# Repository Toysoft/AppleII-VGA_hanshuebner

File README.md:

# ∀2 Retro Computing Analog VGA Card & PicoPal

This is a fork of
[David Kuder's version](https://github.com/V2RetroComputing/analog) of
[Mark Aikens' Apple II VGA](https://github.com/markadev/AppleII-VGA/)
project.

The goal of this fork is to make the board cheaper and easier to
produce.  It is now a 2 layer instead of a 4 layer PCB, uses cheaper
bus transceivers and 0603 passive components that are easier to work
with when building the board by hand.

The board provides a VGA output to Apple II compatible machines.  It works by
snooping the bus activity and capturing what is written to the internal
graphics hardware.  This is used to render an additional image into a
framebuffer on the Raspberry Pi Pico.  That framebuffer is output
to a standard VGA compatible output.

The VGA emulation starts up with a test screen.  Reset your Apple to
go to the BASIC prompt or boot screen.

The footprint of the VGA IDC connector on the board is incorrect.  The
red wire of the ribbon cable must be facing down, in direction of the 
motherboard.  If you get no picture, try rotating the cable.

Alternatively, the card can run a Z80 emulation in software, emulating
a standard Z80 softcard.  To use that mode, the Raspberry Pi Pico must
be re-flashed.

Please use
[GitHub Issues](https://github.com/hanshuebner/AppleII-VGA/issues) to
provide feedback.  THANK YOU!

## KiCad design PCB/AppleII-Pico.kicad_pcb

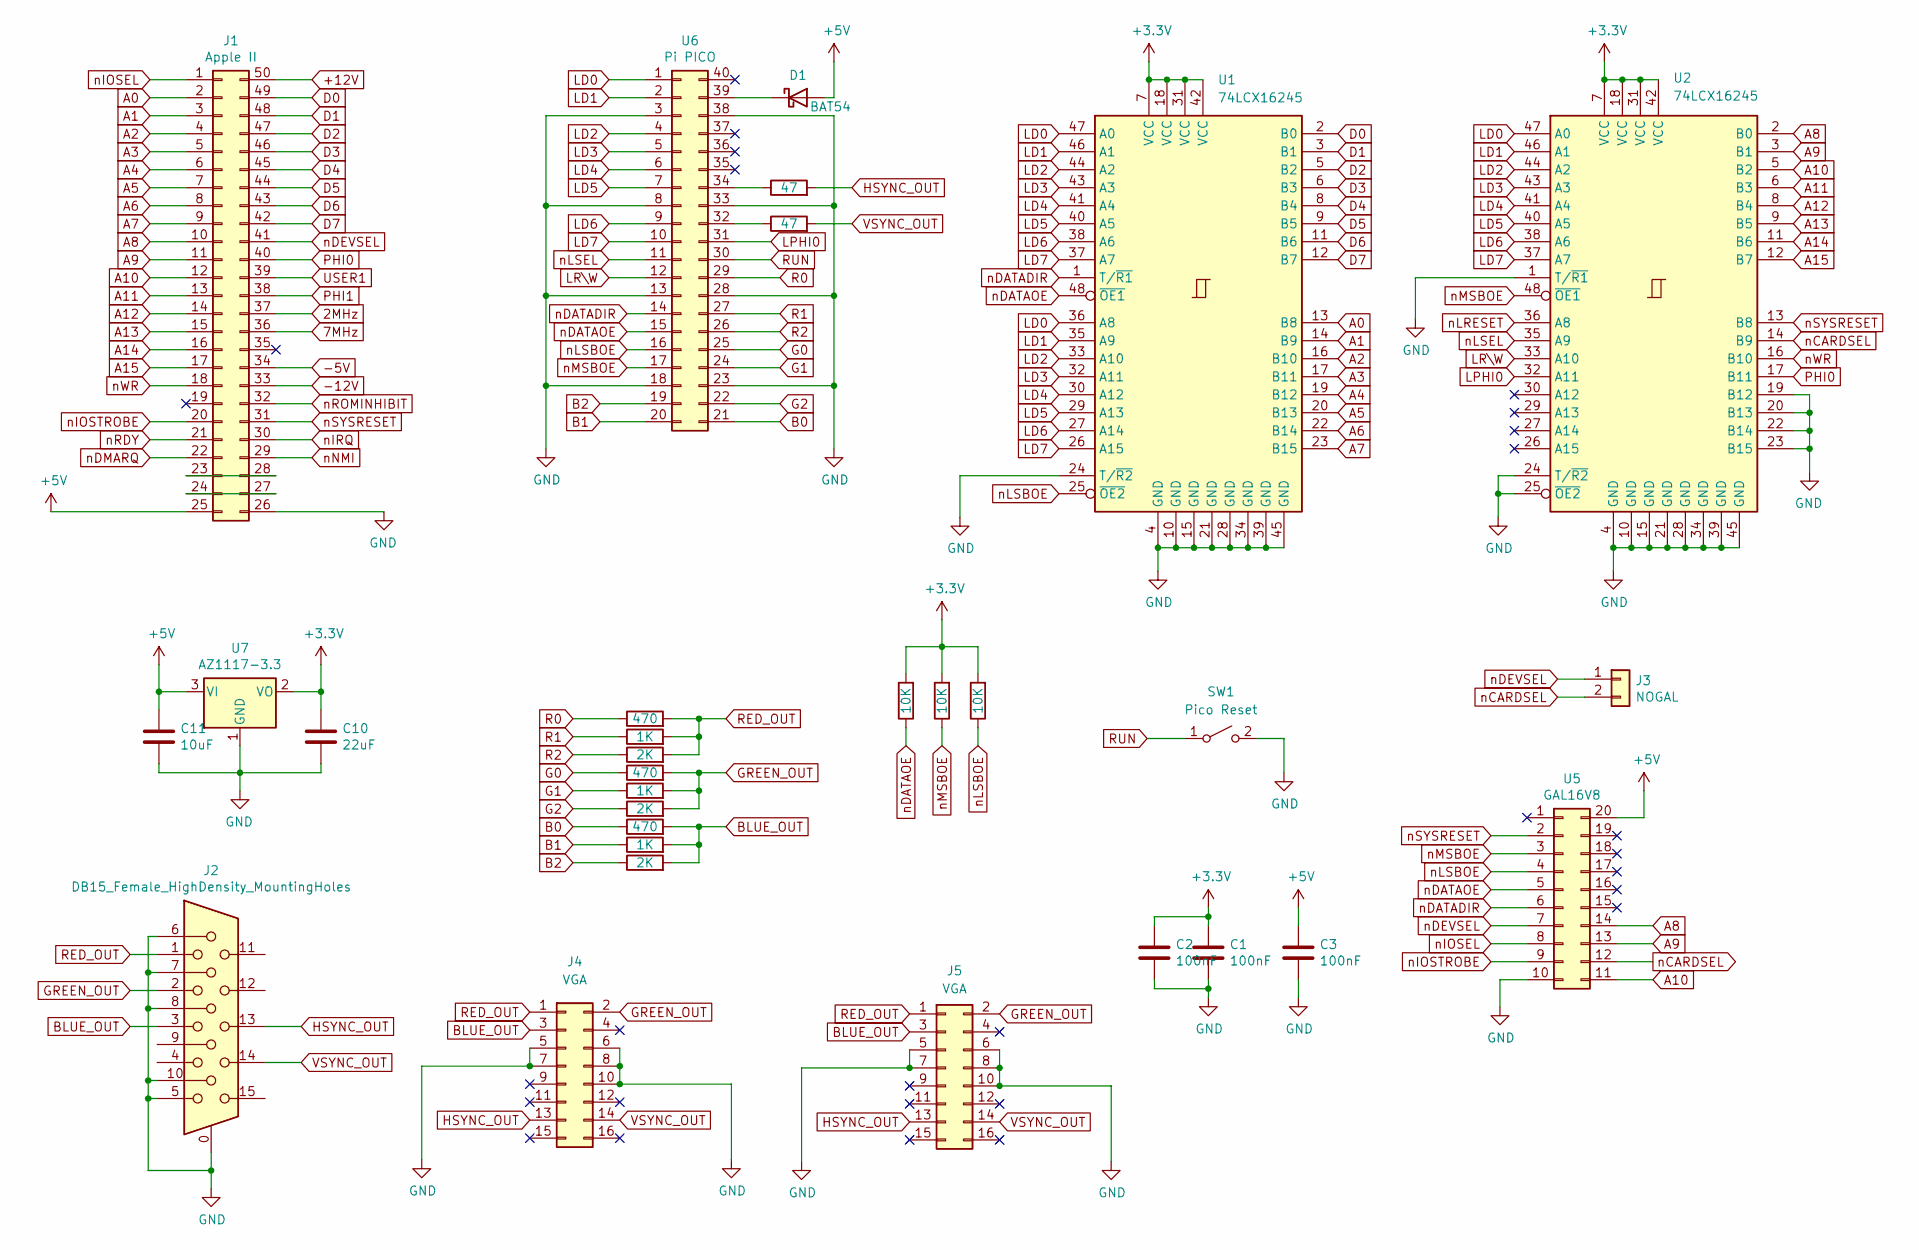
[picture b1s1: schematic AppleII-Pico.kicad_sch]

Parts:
C1, C2, C3: 100nF; C_0603_1608Metric_Pad1.08x0.95mm_HandSolder
C10: 22uF; C_0805_2012Metric_Pad1.18x1.45mm_HandSolder
C11: 10uF; C_0805_2012Metric_Pad1.18x1.45mm_HandSolder
D1: BAT54; D_SMA_Handsoldering
J1: Apple II; AppleII
J2: DB15_Female_HighDensity_MountingHoles; DSUB-15-HD_Female_Horizontal_P2.29x1.98mm_EdgePinOffset3.03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
J3: NOGAL; SolderJumper-2_P1.3mm_Open_TrianglePad1.0x1.5mm
J4, J5: VGA; PinHeader_2x08_P2.54mm_Vertical
R1, R4, R7: 470; R_0603_1608Metric_Pad0.98x0.95mm_HandSolder
R2, R5, R8: 1K; R_0603_1608Metric_Pad0.98x0.95mm_HandSolder
R3, R6, R9: 2K; R_0603_1608Metric_Pad0.98x0.95mm_HandSolder
R10, R11: 47; R_0603_1608Metric_Pad0.98x0.95mm_HandSolder
R12, R13, R14: 10K; R_0603_1608Metric_Pad0.98x0.95mm_HandSolder
SW1: Pico Reset; SW_Push_1P1T_NO_6x6mm_H9.5mm
U1: 74LCX16245; TSSOP-48_6.1x9.7mm_P0.4mm
U2: 74LCX16245; TSSOP-48_6.1x12.5mm_P0.5mm
U5: GAL16V8; PLCC-20
U6: Pi PICO; RPi_Pico_SMD_TH
U7: AZ1117-3.3; SOT-223-3_TabPin2

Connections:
2MHz: J1.37
7MHz: J1.36
+3V3: C1.1, C2.1, C10.1, R12.2, R13.2, R14.2, U1.7 (VCC), U1.18 (VCC), U1.31 (VCC), U1.42 (VCC), U2.7 (VCC), U2.18 (VCC), U2.31 (VCC), U2.42 (VCC), U7.2 (VO)
+5V: C3.1, C11.1, D1.2 (A), J1.25, U5.20, U7.3 (VI)
+12V: J1.50
-5V: J1.34
-12V: J1.33
A0: J1.2, U1.13 (B8)
A1: J1.3, U1.14 (B9)
A2: J1.4, U1.16 (B10)
A3: J1.5, U1.17 (B11)
A4: J1.6, U1.19 (B12)
A5: J1.7, U1.20 (B13)
A6: J1.8, U1.22 (B14)
A7: J1.9, U1.23 (B15)
A8: J1.10, U2.2 (B0), U5.14
A9: J1.11, U2.3 (B1), U5.13
A10: J1.12, U2.5 (B2), U5.11
A11: J1.13, U2.6 (B3)
A12: J1.14, U2.8 (B4)
A13: J1.15, U2.9 (B5)
A14: J1.16, U2.11 (B6)
A15: J1.17, U2.12 (B7)
B0: R7.1, U6.21
B1: R8.1, U6.20
B2: R9.1, U6.19
BLUE_OUT: J2.3, J4.3, J5.3, R7.2, R8.2, R9.2
D0: J1.49, U1.2 (B0)
D1: J1.48, U1.3 (B1)
D2: J1.47, U1.5 (B2)
D3: J1.46, U1.6 (B3)
D4: J1.45, U1.8 (B4)
D5: J1.44, U1.9 (B5)
D6: J1.43, U1.11 (B6)
D7: J1.42, U1.12 (B7)
G0: R4.1, U6.25
G1: R5.1, U6.24
G2: R6.1, U6.22
GND: C1.2, C2.2, C3.2, C10.2, C11.2, J1.26, J2.0, J2.5, J2.6, J2.7, J2.8, J2.10, J4.5, J4.6, J4.7, J4.8, J4.10, J5.5, J5.6, J5.7, J5.8, J5.10, SW1.2 (B), U1.4 (GND), U1.10 (GND), U1.15 (GND), U1.21 (GND), U1.24 (T/~R2), U1.28 (GND), U1.34 (GND), U1.39 (GND), U1.45 (GND), U2.1 (T/~R1), U2.4 (GND), U2.10 (GND), U2.15 (GND), U2.19 (B12), U2.20 (B13), U2.21 (GND), U2.22 (B14), U2.23 (B15), U2.24 (T/~R2), U2.25 (~OE2), U2.28 (GND), U2.34 (GND), U2.39 (GND), U2.45 (GND), U5.10, U6.3, U6.8, U6.13, U6.18, U6.23, U6.28, U6.33, U6.38, U7.1 (GND)
GREEN_OUT: J2.2, J4.2, J5.2, R4.2, R5.2, R6.2
HSYNC_OUT: J2.13, J4.13, J5.13, R10.2
LD0: U1.36 (A8), U1.47 (A0), U2.47 (A0), U6.1
LD1: U1.35 (A9), U1.46 (A1), U2.46 (A1), U6.2
LD2: U1.33 (A10), U1.44 (A2), U2.44 (A2), U6.4
LD3: U1.32 (A11), U1.43 (A3), U2.43 (A3), U6.5
LD4: U1.30 (A12), U1.41 (A4), U2.41 (A4), U6.6
LD5: U1.29 (A13), U1.40 (A5), U2.40 (A5), U6.7
LD6: U1.27 (A14), U1.38 (A6), U2.38 (A6), U6.9
LD7: U1.26 (A15), U1.37 (A7), U2.37 (A7), U6.10
LPHI0: U2.32 (A11), U6.31
LR\W: U2.33 (A10), U6.12
unnamed: D1.1 (K), U6.39
unnamed: J1.23, J1.28
unnamed: J1.24, J1.27
unnamed: R11.1, U6.32
unnamed: R10.1, U6.34
PHI0: J1.40, U2.17 (B11)
PHI1: J1.38
R0: R1.1, U6.29
R1: R2.1, U6.27
R2: R3.1, U6.26
RED_OUT: J2.1, J4.1, J5.1, R1.2, R2.2, R3.2
RUN: SW1.1 (A), U6.30
USER1: J1.39
VSYNC_OUT: J2.14, J4.14, J5.14, R11.2
nCARDSEL: J3.2, U2.14 (B9), U5.12
nDATADIR: U1.1 (T/~R1), U5.6, U6.14
nDATAOE: R12.1, U1.48 (~OE1), U5.5, U6.15
nDEVSEL: J1.41, J3.1, U5.7
nDMARQ: J1.22
nIOSEL: J1.1, U5.8
nIOSTROBE: J1.20, U5.9
nIRQ: J1.30
nLRESET: U2.36 (A8)
nLSBOE: R14.1, U1.25 (~OE2), U5.4, U6.16
nLSEL: U2.35 (A9), U6.11
nMSBOE: R13.1, U2.48 (~OE1), U5.3, U6.17
nNMI: J1.29
nRDY: J1.21
nROMINHIBIT: J1.32
nSYSRESET: J1.31, U2.13 (B8), U5.2
nWR: J1.18, U2.16 (B10)

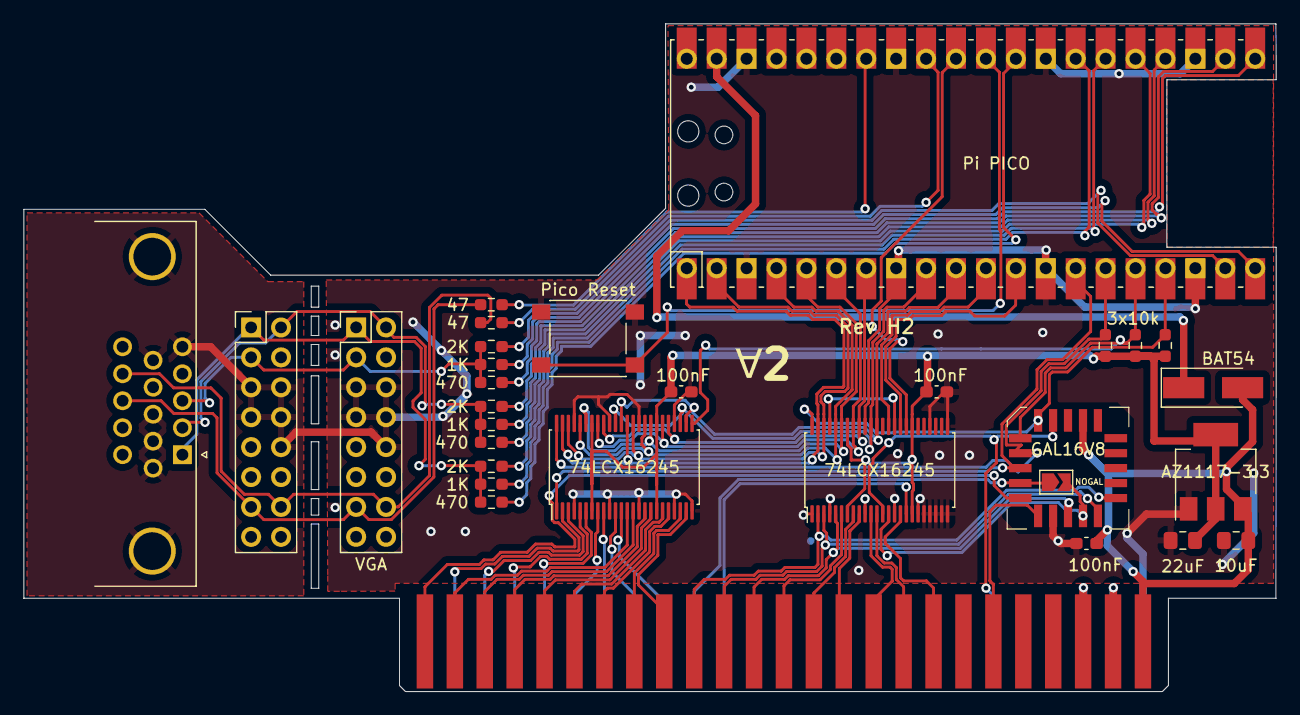
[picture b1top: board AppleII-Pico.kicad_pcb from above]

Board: 2 copper layers, 106.3 x 56.7 mm, 31 parts (0 on the bottom side), 69 nets.

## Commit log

2023-03-25 Rework PCB to make it more DIY-friendly
    - Use 2 layer PCB
    - Replace bus transceivers by cheaper and easier to find 74LCX16245
    - Put component values on silkscreen
    - Replace 0402 passives with 0603's
    - Add IDC header for VGA breakout cable
2023-03-25 Rename schematics file
2023-03-26 Make space for THT DIP socket
2023-03-26 Better RPi Pico footprint
2023-03-26 more space for the USB connector
2023-03-26 Update image
2023-03-26 DRC fixes
2023-03-26 beauty tweaks
2023-03-26 incorporate feedback
    - Pico W antenna cutout
    - Pico RUN button
    - Break-away HD15A connector
2023-03-26 Update images and schematics PDF
2023-03-26 RUN => Pico Reset
2023-03-26 fix db15hd footprint
2023-03-26 Update gerber directory
2023-03-28 tweaks before sending to JLCPCB
2023-04-24 Fix TSSOP-48 footprint and move NOPAL
    - Use correct footprint for the TSSOP-48 case (closes #2)
    - Rename NOPAL to NOGAL and move it into the GAL footprint (closes #3)
2023-04-27 Add image
2023-04-27 _actually_ add it
2023-04-27 silkscreen tweaks
    closes #4
2023-05-10 Version h2 sent to JLCPCB for production
2023-05-30 Add BOM and production files

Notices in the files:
PCB/AppleII-Pico.kicad_pcb:
Copyright © 2022
